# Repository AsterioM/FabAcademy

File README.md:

# FabAcademy
in this repository you can find files from http://archive.fabacademy.org/archives/2017/fablabbcn/students/29/

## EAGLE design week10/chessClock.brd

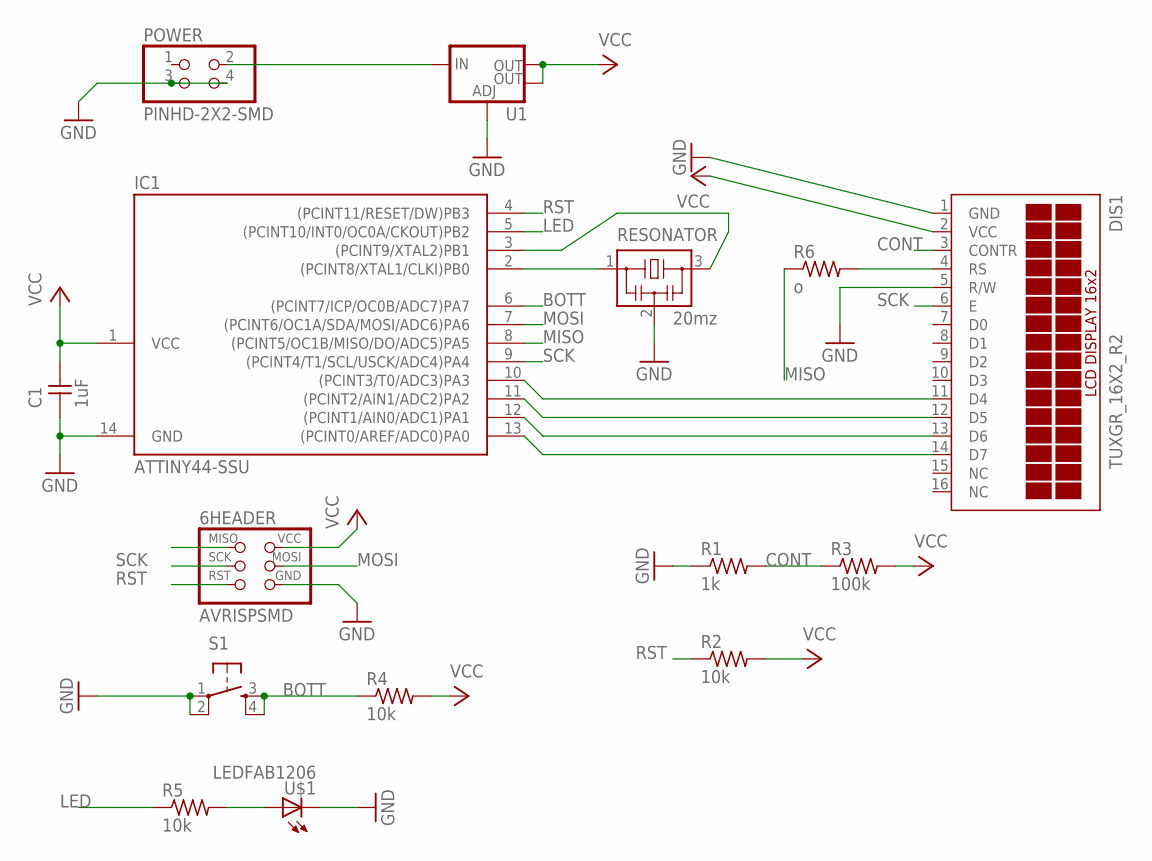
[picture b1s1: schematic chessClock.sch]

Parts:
6HEADER: AVRISPSMD; 2X03SMD
C1: 1uF; C1206FAB
DIS1: TUXGR_16X2_R2
IC1: ATTINY44-SSU; SOIC14
POWER: PINHD-2X2-SMD; 2X02SMD
R1: 1k; R1206FAB
R2, R4, R5: 10k; R1206FAB
R3: 100k; R1206FAB
R6: o; R1206FAB
RESONATOR: 20mz; EFOBM
S1: 6MM_SWITCH6MM_SWITCH; 6MM_SWITCH
U1: V_REG_LM1117SOT223; SOT223
U$1: LEDFAB1206; LED1206FAB

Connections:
BOTT: IC1.6 ((PCINT7/ICP/OC0B/ADC7)PA7), R4.1, S1.3 (S), S1.4 (S1)
CONT: DIS1.3 (CONTR), R1.2, R3.1
GND: 6HEADER.6 (GND), C1.1, DIS1.1 (GND), DIS1.5 (R/W), IC1.14 (GND), POWER.3, POWER.4, R1.1, RESONATOR.2, S1.1, S1.2 (P1), U1.1 (ADJ), U$1.2 (C)
LED: IC1.5 ((PCINT10/INT0/OC0A/CKOUT)PB2), R5.1
MISO: 6HEADER.1 (MISO), IC1.8 ((PCINT5/OC1B/MISO/DO/ADC5)PA5), R6.1
MOSI: 6HEADER.4 (MOSI), IC1.7 ((PCINT6/OC1A/SDA/MOSI/ADC6)PA6)
unnamed: IC1.3 ((PCINT9/XTAL2)PB1), RESONATOR.3
unnamed: IC1.2 ((PCINT8/XTAL1/CLKI)PB0), RESONATOR.1
unnamed: DIS1.14 (D7), IC1.13 ((PCINT0/AREF/ADC0)PA0)
unnamed: DIS1.13 (D6), IC1.12 ((PCINT1/AIN0/ADC1)PA1)
unnamed: DIS1.12 (D5), IC1.11 ((PCINT2/AIN1/ADC2)PA2)
unnamed: DIS1.11 (D4), IC1.10 ((PCINT3/T0/ADC3)PA3)
unnamed: POWER.2, U1.3 (IN)
unnamed: DIS1.4 (RS), R6.2
unnamed: R5.2, U$1.1 (A)
RST: 6HEADER.5 (RST), IC1.4 ((PCINT11/RESET/DW)PB3), R2.1
SCK: 6HEADER.3 (SCK), DIS1.6 (E), IC1.9 ((PCINT4/T1/SCL/USCK/ADC4)PA4)
VCC: 6HEADER.2 (VCC), C1.2, DIS1.2 (VCC), IC1.1 (VCC), R2.2, R3.2, R4.2, U1.2 (OUT), U1.4 (OUT)

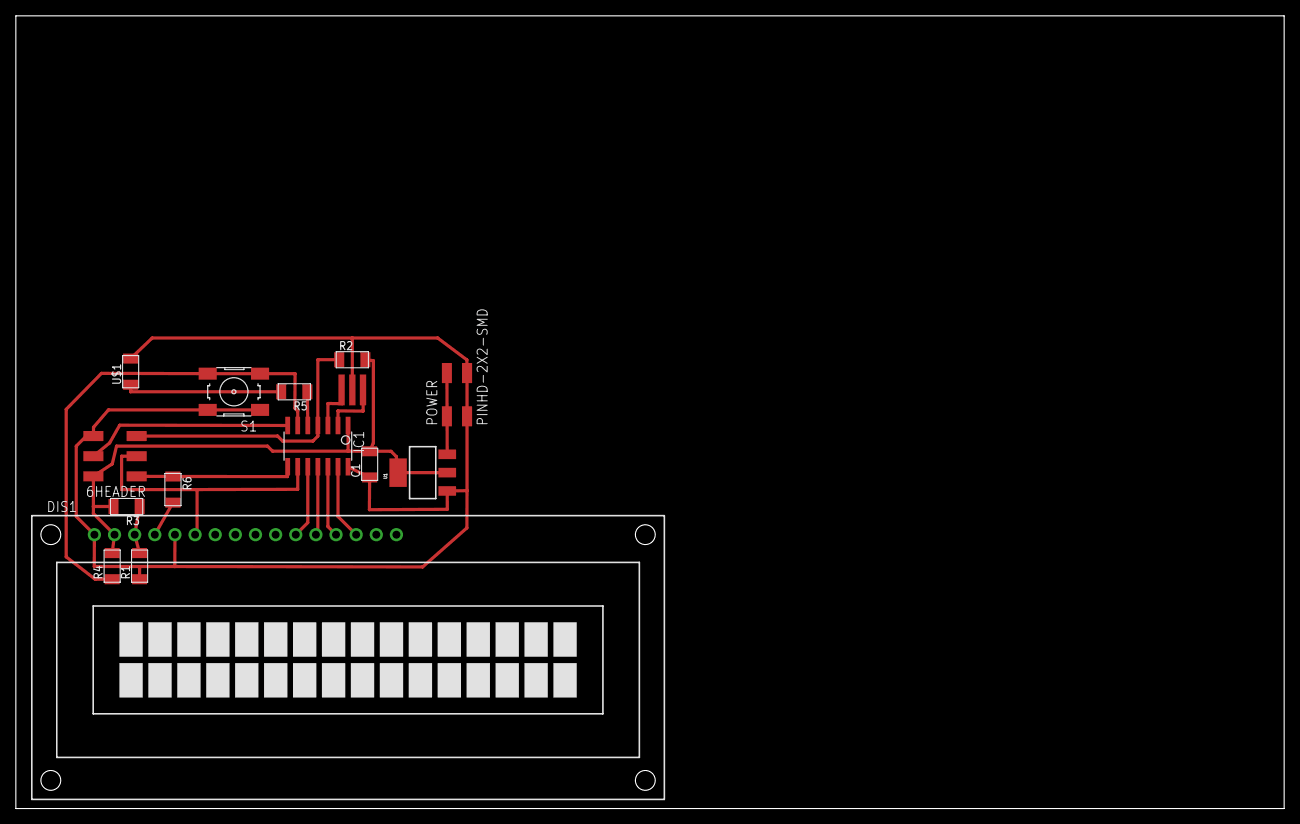
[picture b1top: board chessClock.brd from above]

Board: 2 copper layers, 160.0 x 100.0 mm, 15 parts (0 on the bottom side), 18 nets.

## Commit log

2017-02-02 solidworks y video
2017-02-06 primera subida desde casa
2017-02-07 zip issu
2017-02-07 me comi un rinoceronte
2017-02-08 add swlasercutframe
2017-02-10 swweek3
2017-02-11 pegatinas_y_presfit
2017-02-11 fotito
2017-02-15 nose
2017-02-16 joder
2017-03-02 w04_funda_files
2017-03-05 dxf_w03
2017-03-05 aegle_files
2017-03-06 fablib
2017-03-11 redme
2017-03-11 corr
2017-03-13 w07swyrhinnozip
2017-04-05 twoinocodes
2017-04-05 eagle
2017-04-05 eagle.zip
2017-04-18 piezes disenyadas para wlly
2017-04-18 wally2
2017-05-02 eagle_thermistor
2017-05-02 gimpthermistor
2017-05-02 datashetpdf
2017-05-08 skateRhinoFilesShotbot
2017-05-16 netw
2017-06-25 cheesW10
2017-06-25 codew08
2017-06-27 w16SimplePlot
2017-06-27 fina
2017-06-27 stlextruder
2017-06-28 SWhandle
2017-06-28 inputcode
2017-06-28 W12files
2017-07-17 grup3
2017-10-11 11oct17
2017-12-08 atril
2018-02-10 hola
